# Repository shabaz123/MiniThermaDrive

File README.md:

# MiniThermaDrive

A controller for heating small objects to user-defined temperatures.

## Overview

This repository contains a project for controlling a small heating element, with feedback using a thermistor. The system provides precise temperature control for various applications.

## Applications

The project is applicable for a variety of uses, including:
- Heating small leather tools
- Warming up a 3D printer bed
- Any application requiring controlled heating of small objects

## Hardware

The element and thermistor happen to be low-cost 3D printer spares, making this an affordable solution for temperature-controlled heating applications.

The project is built on two circuit boards; a Driver Board, and a Control Board.

## Driver Board

The Driver Board provides connections to the heater element, sensor (thermistor) and to the 24V DC input.

The other side of the Driver Board contains the driver circuitry (a MOSFET), and a 5V DC supply, for powering the microcontroller on the Control Board.

The Driver Board connects to the Control Board using an 8-way JST-PH connector cable.

Driver Board circuit diagram:

## Control Board

TBD. 

The Control board contains the microcontroller, and the user interface (a rotary potentiometer for setting the desired temperature, and a little TFT screen for displaying the set temperature, and the actual temperature).

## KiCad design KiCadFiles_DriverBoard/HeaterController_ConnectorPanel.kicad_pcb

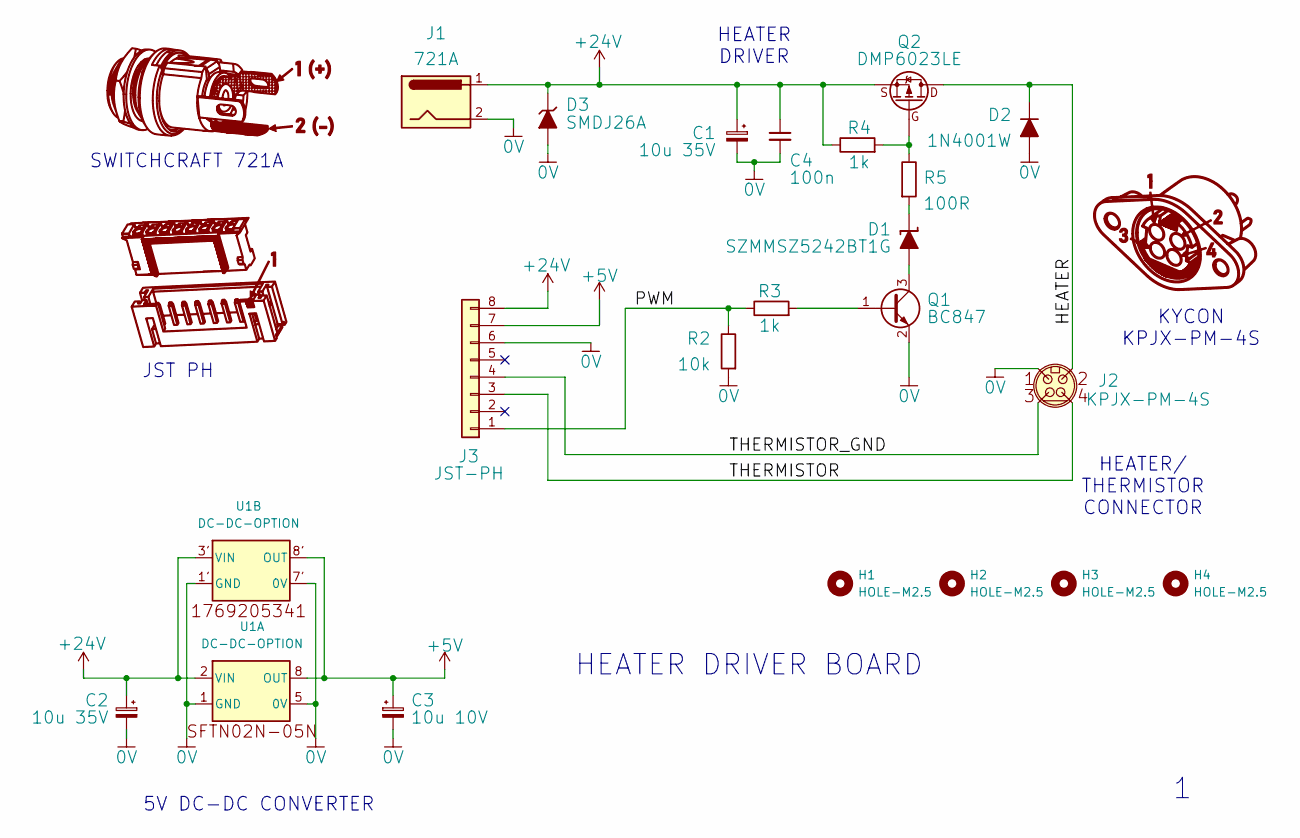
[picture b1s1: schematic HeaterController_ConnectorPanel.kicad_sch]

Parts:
C1, C2: 10u 35V; Cap-Electrolytic-SMD-Pana-Case-C
C3: 10u 10V; Cap-Tant-CaseB
C4: 100n; C_0805_2012Metric_Pad1.18x1.45mm_HandSolder
D1: SZMMSZ5242BT1G; D_SOD-123-pins12
D2: 1N4001W; D_SOD-123-pins12
D3: SMDJ26A; DO-214AB-TVS-UNIDIR
H1, H2, H3, H4: HOLE-M2.5; MountingHole_2.7mm
J1: 721A; DC-JACK-721A-PanelMount
J2: KPJX-PM-4S
J3: JST-PH; JST_PH_8WAY-VERT-SMD-B8B-PH-SM4-TB
Q1: BC847; SOT-23
Q2: DMP6023LE; SOT-223
R2: 10k; R_0805_2012Metric_Pad1.20x1.40mm_HandSolder
R3, R4: 1k; R_0805_2012Metric_Pad1.20x1.40mm_HandSolder
R5: 100R; R_0805_2012Metric_Pad1.20x1.40mm_HandSolder
U1: DC-DC-OPTION; DC-DC-COMBINED-SMD

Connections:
0V: C1.2, C2.2, C3.2, C4.2, D2.2 (A), D3.2 (A), J1.2, J2.1, J3.6, Q1.2 (E), R2.2, U1.1 (GND), U1.1' (GND), U1.5 (0V), U1.7' (0V)
+5V: C3.1, J3.7, U1.8 (OUT), U1.8' (OUT)
+24V: C1.1, C2.1, C4.1, D3.1 (K), J1.1, J3.8, Q2.3 (S), R4.1, U1.2 (VIN), U1.3' (VIN)
/HEATER: D2.1 (K), J2.2, Q2.2 (D)
/PWM: J3.1, R2.1, R3.1
/THERMISTOR: J2.4, J3.3
/THERMISTOR_GND: J2.3, J3.4
unnamed: D1.2 (A), Q1.3 (C)
unnamed: D1.1 (K), R5.2
unnamed: Q1.1 (B), R3.2
unnamed: Q2.1 (G), R4.2, R5.1

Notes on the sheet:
JST PH
HEATER DRIVER BOARD
HEATER DRIVER
SWITCHCRAFT 721A
KYCON KPJX-PM-4S
HEATER/ THERMISTOR CONNECTOR
5V DC-DC CONVERTER

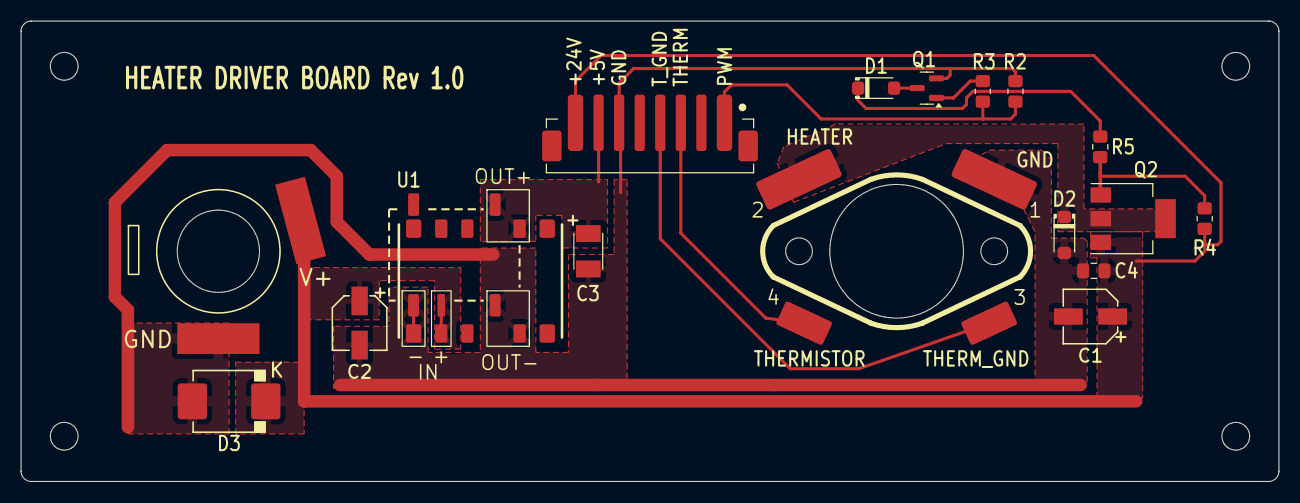
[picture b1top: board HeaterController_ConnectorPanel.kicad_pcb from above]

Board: 2 copper layers, 122.4 x 44.8 mm, 21 parts (0 on the bottom side), 11 nets.

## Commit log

2025-11-05 Initial plan
2025-11-05 Update README with comprehensive project description
2025-11-05 Expand README with Driver and Control Board details
    Added detailed descriptions of the Driver Board and Control Board components, including images and functionality.
